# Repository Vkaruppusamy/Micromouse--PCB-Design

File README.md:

# Micromouse--PCB-Design
This is a micromouse pcd desgin, which is desinged completly using the kicad 8.0 software. And sucessfully fabricated and converted into a product
The complete pics of the Micromouse

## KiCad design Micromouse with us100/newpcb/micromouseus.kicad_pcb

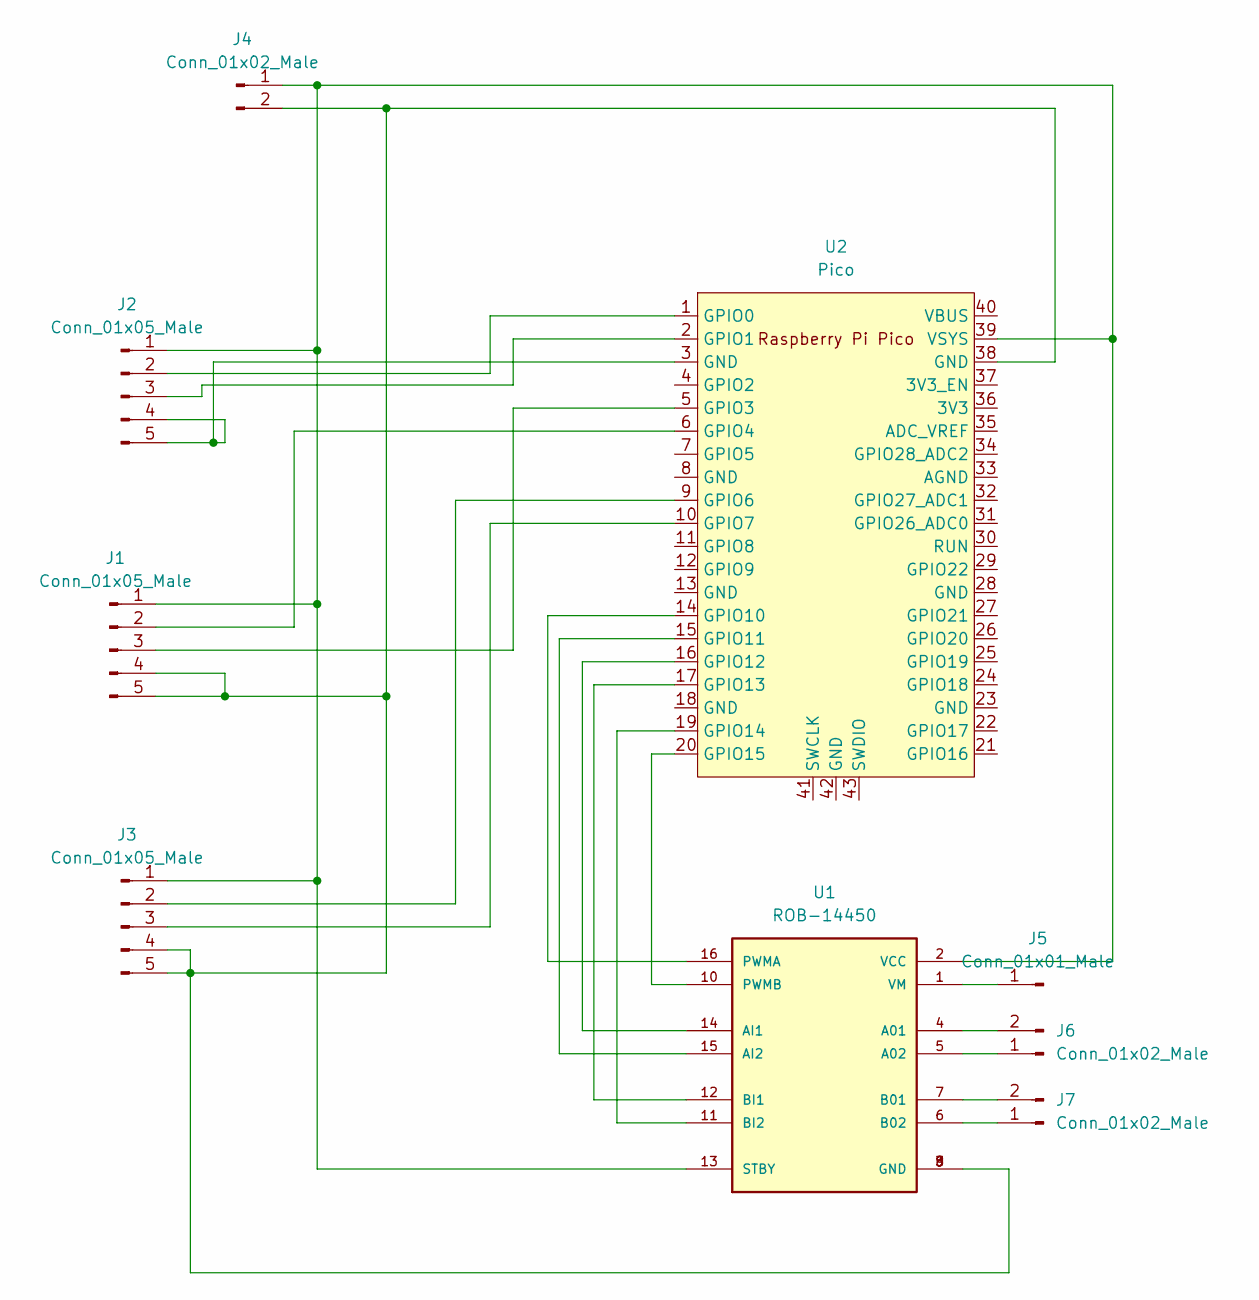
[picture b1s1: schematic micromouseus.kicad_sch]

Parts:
J1, J2, J3: Conn_01x05_Male; PinHeader_1x05_P2.54mm_Vertical
J4, J6, J7: Conn_01x02_Male; PinHeader_1x02_P2.54mm_Vertical
J5: Conn_01x01_Male; PinHeader_1x01_P2.54mm_Vertical
U1: ROB-14450; MODULE_ROB-14450; PARTREV 11-13-17
U2: Pico; RPi_Pico_SMD_TH

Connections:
unnamed: J1.1, J2.1, J3.1, J4.1, U1.2 (VCC), U1.13 (STBY), U2.39 (VSYS)
unnamed: J1.2, U2.6 (GPIO4)
unnamed: J1.3, U2.5 (GPIO3)
unnamed: J1.4, J1.5, J3.4, J3.5, J4.2, U1.3 (GND), U1.8 (GND), U1.9 (GND), U2.38 (GND)
unnamed: J2.2, U2.1 (GPIO0)
unnamed: J2.3, U2.2 (GPIO1)
unnamed: J3.2, U2.9 (GPIO6)
unnamed: J3.3, U2.10 (GPIO7)
unnamed: J5.1, U1.1 (VM)
unnamed: J6.1, U1.5 (A02)
unnamed: J6.2, U1.4 (A01)
unnamed: J7.1, U1.6 (B02)
unnamed: J7.2, U1.7 (B01)
unnamed: U1.10 (PWMB), U2.20 (GPIO15)
unnamed: U1.11 (BI2), U2.19 (GPIO14)
unnamed: U1.12 (BI1), U2.17 (GPIO13)
unnamed: U1.14 (AI1), U2.16 (GPIO12)
unnamed: U1.15 (AI2), U2.15 (GPIO11)
unnamed: U1.16 (PWMA), U2.14 (GPIO10)
unnamed: J2.4, J2.5, U2.3 (GND)

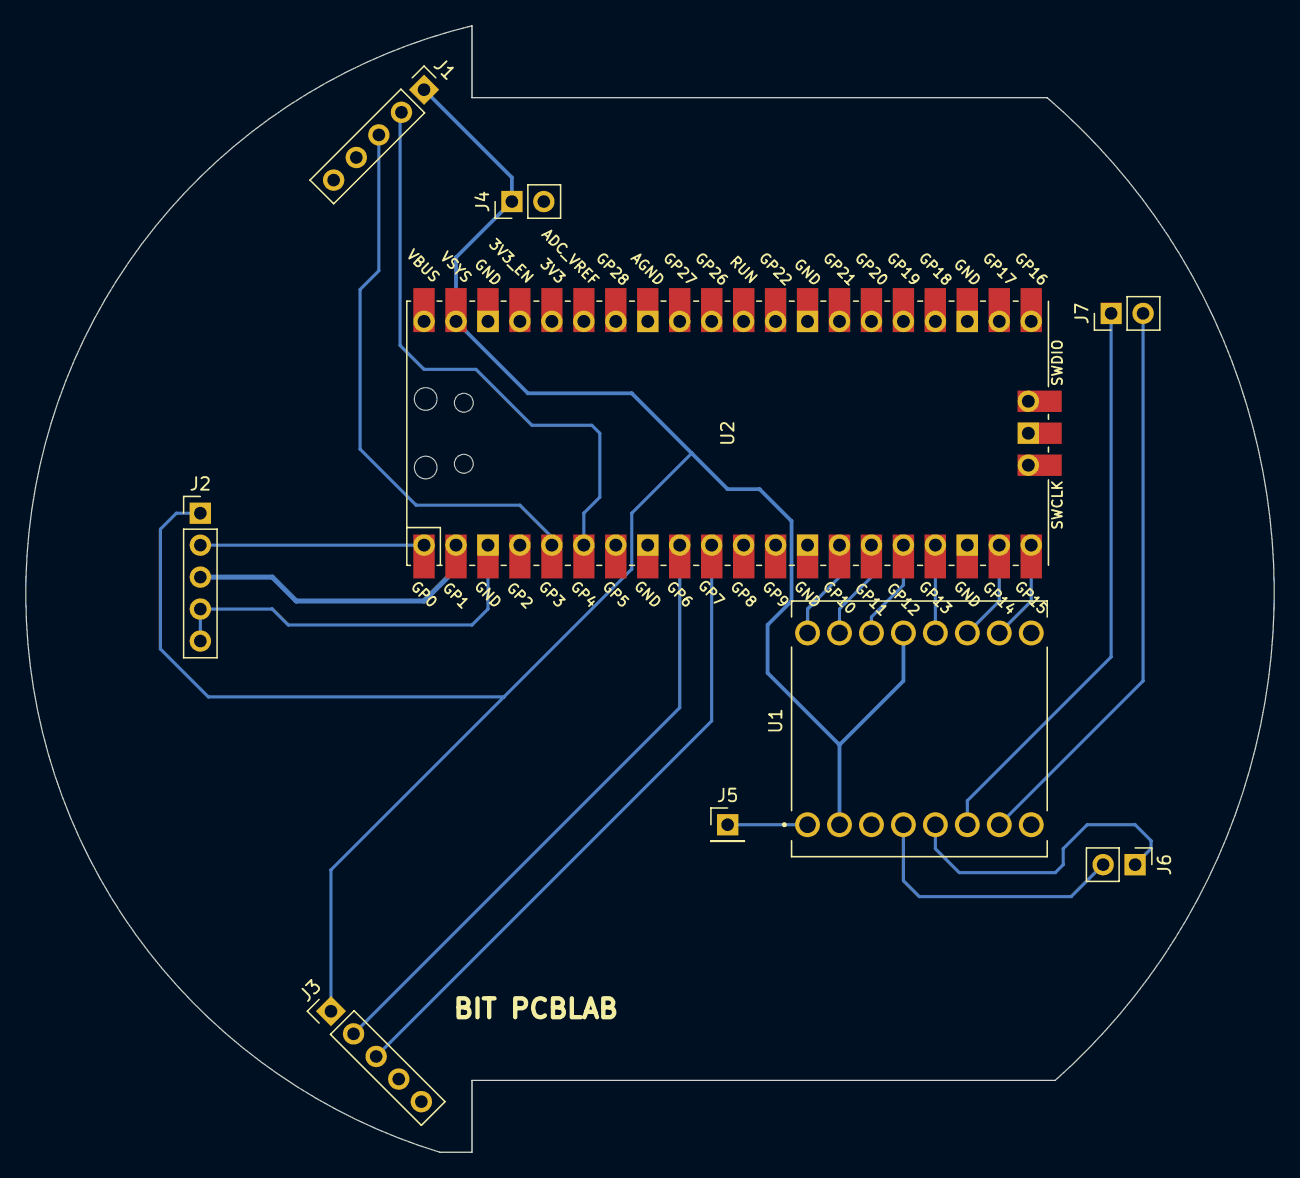
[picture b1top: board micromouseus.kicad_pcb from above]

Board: 2 copper layers, 99.2 x 89.5 mm, 9 parts (0 on the bottom side), 20 nets.

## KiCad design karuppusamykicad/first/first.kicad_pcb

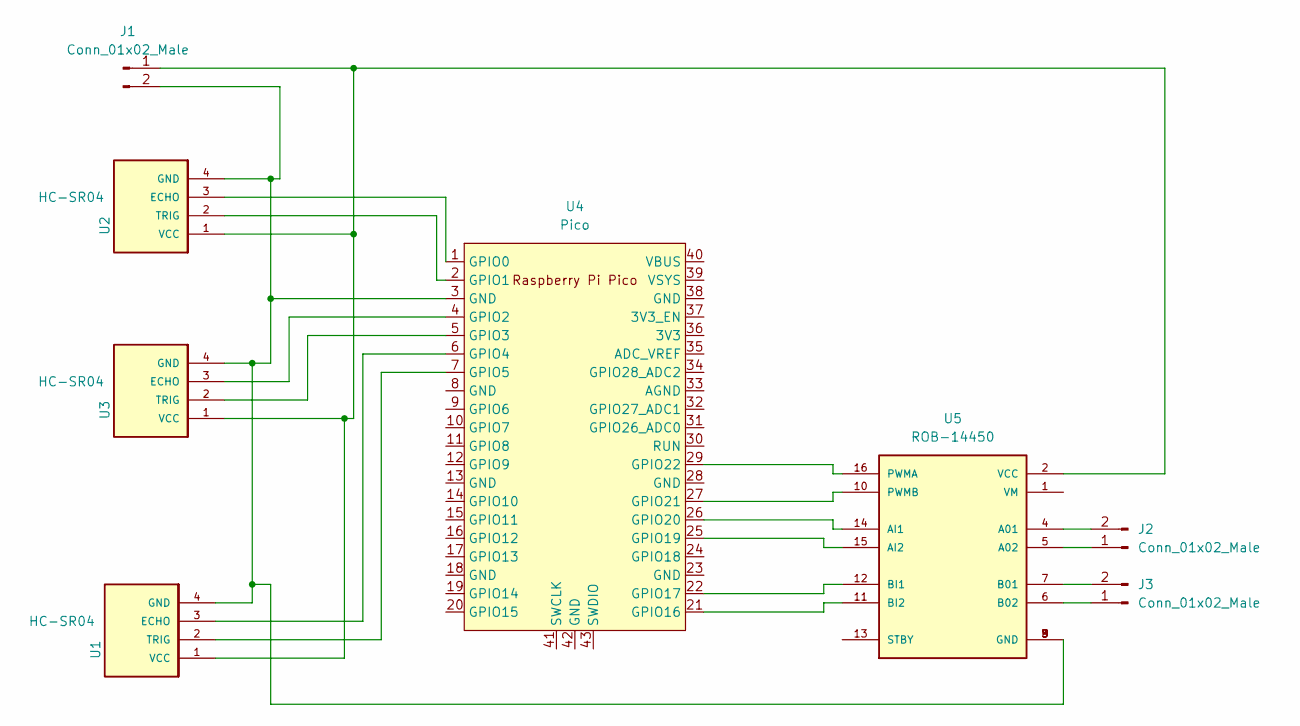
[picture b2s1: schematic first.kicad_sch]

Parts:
J1, J3: Conn_01x02_Male; PhoenixContact_MSTBA_2,5_2-G_1x02_P5.00mm_Horizontal
J2: Conn_01x02_Male; PhoenixContact_MSTBA_2,5_2-G-5,08_1x02_P5.08mm_Horizontal
U1, U2, U3: HC-SR04; XCVR_HC-SR04
U4: Pico; RPi_Pico_SMD_TH
U5: ROB-14450; MODULE_ROB-14450; PARTREV 11-13-17

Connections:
unnamed: J1.1, U1.1 (VCC), U2.1 (VCC), U3.1 (VCC), U5.2 (VCC)
unnamed: J1.2, U1.4 (GND), U2.4 (GND), U3.4 (GND), U4.3 (GND), U5.3 (GND), U5.8 (GND), U5.9 (GND)
unnamed: J2.1, U5.5 (A02)
unnamed: J2.2, U5.4 (A01)
unnamed: J3.1, U5.6 (B02)
unnamed: J3.2, U5.7 (B01)
unnamed: U1.2 (TRIG), U4.7 (GPIO5)
unnamed: U1.3 (ECHO), U4.6 (GPIO4)
unnamed: U2.2 (TRIG), U4.2 (GPIO1)
unnamed: U2.3 (ECHO), U4.1 (GPIO0)
unnamed: U3.2 (TRIG), U4.5 (GPIO3)
unnamed: U3.3 (ECHO), U4.4 (GPIO2)
unnamed: U4.21 (GPIO16), U5.11 (BI2)
unnamed: U4.22 (GPIO17), U5.12 (BI1)
unnamed: U4.25 (GPIO19), U5.15 (AI2)
unnamed: U4.26 (GPIO20), U5.14 (AI1)
unnamed: U4.27 (GPIO21), U5.10 (PWMB)
unnamed: U4.29 (GPIO22), U5.16 (PWMA)

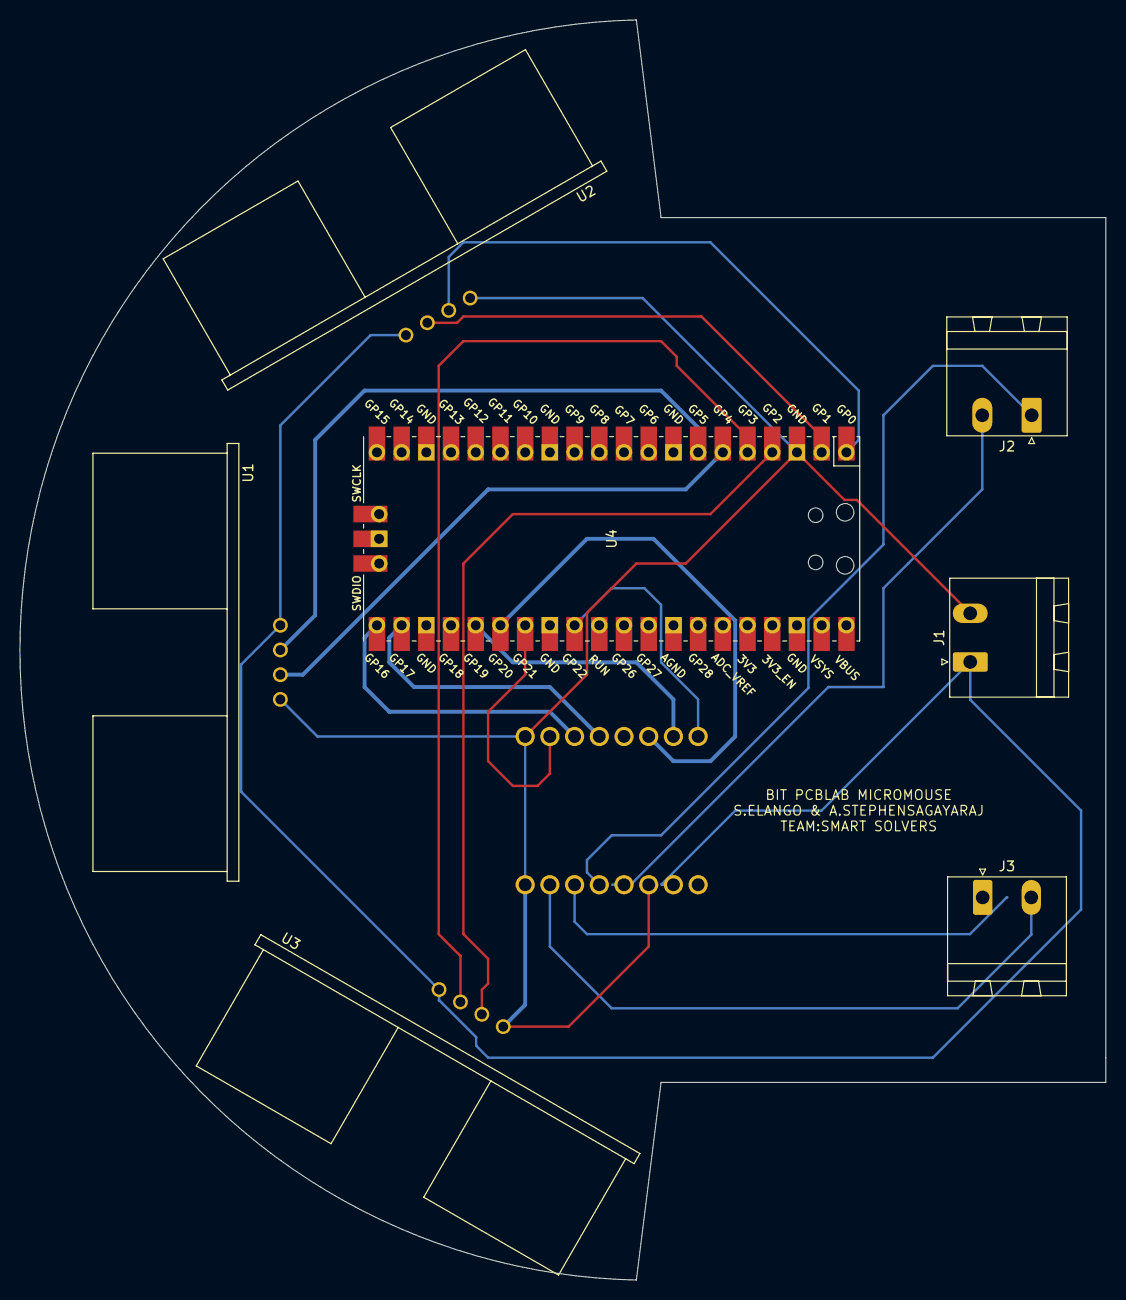
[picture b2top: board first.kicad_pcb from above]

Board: 2 copper layers, 111.6 x 129.5 mm, 8 parts (1 on the bottom side), 18 nets.

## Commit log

2024-03-24 Create PCB DESIGN
